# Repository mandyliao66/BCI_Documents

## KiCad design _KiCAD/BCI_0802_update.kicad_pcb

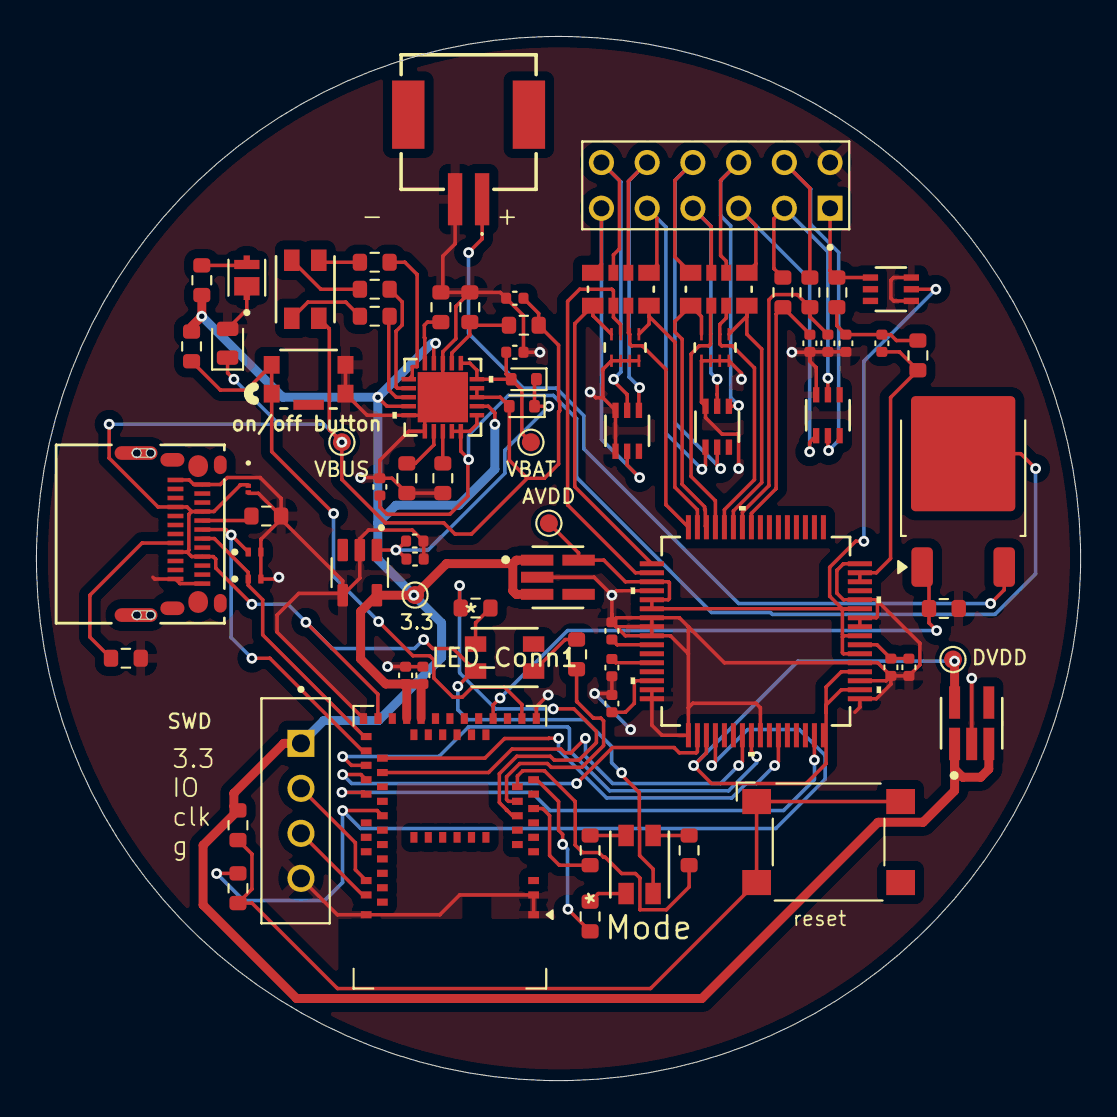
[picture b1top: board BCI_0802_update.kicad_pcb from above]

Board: 2 copper layers, 58.0 x 58.0 mm, 76 parts (0 on the bottom side), 72 nets.

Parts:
C1, C3, C7, C10, C12: 1uF; C_0402_1005Metric
C2, C4, C17: 10uF; C_0402_1005Metric
C5, C18, C19, C20: 1000pF; C_0402_1005Metric
C6: 0.1uF; C_0402_1005Metric
C11: 100uF; C_0402_1005Metric
C15, C16: 4.7uF; C_0402_1005Metric
C21, C24: CKCL44X7R1H102M085AA; CKCL44_TDK
CR1: ESD441DPLR; X2SON2_DPL_TEX
D1, D2: 1N4148WT; D_SOD-523
D3, D5: ESD321DPYR; TVS_ESD321DPYR
D4: MP-2016-1100-50-70; LED_MP-2016-1100-50-70
D6: BZM55Bxx; D_MicroMELF
J1: SM02B-ZESS-TB_LF__SN_; SM02BZESSTBLFSN
J2: 87227-6; TE_87227-6
J3: B4B-EH-A; JST_B4B-EH-A
LED_Conn1: CLV1A-FKB-CK1VW1DE1BB7C3C3; CLV1A-FKB-CK1VW1DE1BB7C3C3_CRE
LED_Op_Mode1: CLV1A-FKB-CK1VW1DE1BB7C3C3; CLV1A-FKB-CK1VW1DE1BB7C3C3_CRE
LED_chargingstate1: CLV1A-FKB-CK1VW1DE1BB7C3C3; CLV1A-FKB-CK1VW1DE1BB7C3C3_CRE
Q1: SUD08P06-155L; TO-252-2
R1, R4: 5.1k; R_0603_1608Metric
R2, R5, R8: 10k; R_0603_1608Metric
R3: 1M; R_0603_1608Metric
R6: 110k; R_0603_1608Metric
R7: 330k; R_0603_1608Metric
R9, R10, R11, R18, R19, R21, R23, R24: 470; R_0603_1608Metric
R12, R13, R14, R15, R16: 2.2k; R_0603_1608Metric
R17, R22: CAY16-2201F4LF; CAY16_BRN
R20, R25: 33; R_0603_1608Metric
R26: 4.7k; R_0603_1608Metric
S1: B3FS-4002P; SW_SPST_Omron_B3FS-100xP
SW1: KMR221GLFS; SW4_KMR221GLFS_CNK
TP1: VBUS; TestPoint_Pad_D1.0mm
TP2: VBAT; TestPoint_Pad_D1.0mm
TP3: 3.3; TestPoint_Pad_D1.0mm
TP4: AVDD; TestPoint_Pad_D1.0mm
TP5: DVDD; TestPoint_Pad_D1.0mm
U1: USB-C31-S-RA-CS2-SMT-BK-T/R; USB-C31-S-RA-CS2-SMT-BK-T&slash_R_ADM
U2: ADS1299-4PAG; PAG64_TEX
U3: TPS78233DDCT; SOT95P280X110-5N
U4: TPS7A2030PDBVR; DBV0005A-IPC_A
U5: TPS7A2018PDBVR; DBV0005A-IPC_A
U6: MCP73871-2AAI/ML; QFN20_4x4MC_MCH
U7, U8, U9, U11: TPD4E1B06DCKR; DCK6_TEX
U10: MDBT50Q-1MV2; Raytac_MDBT50Q

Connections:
/1N: J2.5, R22.1, U8.4 (IO3)
/1P: J2.11, R22.2, U9.1 (IO1)
/2N: J2.4, R17.3, U8.2 (IO2)
/2P: J2.10, R17.4, U8.5 (IO4)
/3.3V: C2.2, C3.2, J3.1, R2.2, R5.2, R26.2, TP3.1, U3.5 (OUT), U4.1 (IN), U4.3 (EN), U5.1 (IN), U5.3 (EN), U6.4 (PROG2), U6.9 (*TE), U6.17 (CE), U10.28 (VDD), U10.30 (VDDH)
/3N: J2.3, R17.1, U7.4 (IO3)
/3P: J2.9, R17.2, U8.1 (IO1)
/4N: J2.2, R15.2, U7.2 (IO2)
/4P: J2.8, R16.2, U7.5 (IO4)
/AVDD: TP4.1, U2.19 (AVDD), U2.21 (AVDD), U2.22 (AVDD), U2.54 (AVDD1), U2.56 (AVDD), U2.59 (AVDD), U4.5 (OUT), U11.2 (IO2)
/BAT+: J1.1, Q1.3 (S)
/BIAS: J2.1, R14.2, U11.4 (IO3)
/BIAS_DRV: C5.1, C20.2, R3.1, R14.1
/Button_on: R5.1, SW1.1, SW1.2, U10.16 (P0.27)
/CS: U2.39 (*CS), U10.38 (P0.16)
/DNEG: D5.1, U1.A7 (DN1), U10.34 (D-)
/DPOS: D3.1, U1.A6 (DP1), U10.35 (D+)
/DRDY: U2.47 (*DRDY), U10.41 (P0.17)
/DVDD: TP5.1, U2.35 (*PWDN), U2.48 (DVDD), U2.50 (DVDD), U2.52 (CLKSEL), U5.5 (OUT)
/IN1N: C24.5, R22.8, U2.15 (IN1N)
/IN1P: C24.6, R22.7, U2.16 (IN1P)
/IN2N: C21.7, R17.6, U2.13 (IN2N)
/IN2P: C21.8, R17.5, U2.14 (IN2P)
/IN3N: C21.5, R17.8, U2.11 (IN3N)
/IN3P: C21.6, R17.7, U2.12 (IN3P)
/IN4N: C19.2, R15.1, U2.9 (IN4N)
/IN4P: C18.2, R16.1, U2.10 (IN4P)
/MISO: U2.43 (DOUT), U10.36 (P0.14)
/MOSI: U2.34 (DIN), U10.39 (P0.15)
/RESET: R25.1, U2.36 (*RESET), U10.43 (P0.21)
/SCLK: U2.40 (SCLK), U10.37 (P0.13)
/SRB1: J2.6, R22.4, U9.5 (IO4)
/SRB2: J2.12, R22.3, U9.2 (IO2)
/SWDCLK: J3.3, U10.53 (SWDCLK)
/SWDIO: J3.2, U10.51 (SWDIO)
/VBAT: C16.2, Q1.2 (D), U6.14 (VBAT), U6.15 (VBAT), U6.16 (VBAT_SENSE)
/VBAT_OUT: C15.2, D1.2 (A), TP2.1, U6.1 (OUT), U6.20 (OUT)
/VBUS: C17.2, CR1.1 (I/O), D2.2 (A), D6.1 (K), LED_Conn1.2, LED_Op_Mode1.2, LED_chargingstate1.2, R7.2, TP1.1, U1.A4 (VBUS), U1.A9 (VBUS), U1.B4 (VBUS), U1.B9 (VBUS), U6.18 (IN), U6.19 (IN), U10.32 (VBUS)
/_SRB1: C24.8, R22.5, U2.17 (SRB1)
/_SRB2: C24.7, R22.6, U2.18 (SRB2)
GNDA: C1.2, C2.1, C3.1, C4.1, C6.2, C7.2, C10.2, C11.2, C12.2, C15.1, C16.1, C17.1, C18.1, C19.1, C20.1, C21.1, C21.2, C21.3, C21.4, C24.1, C24.2, C24.3, C24.4, CR1.2 (GND), D3.2, D4.C, D5.2, D6.2 (A), J1.2, J3.4, R1.1, R4.2, R6.2, R8.2, R12.1, R13.1, R20.2, SW1.3, SW1.4, U1.A1 (GND), U1.A12 (GND), U1.B1 (GND), U1.B12 (GND), U2.20 (AVSS), U2.23 (AVSS), U2.24 (VREFP), U2.25 (VREFN), U2.31 (RESV1), U2.32 (AVSS), U2.33 (DGND), U2.41 (DAISY_IN), U2.49 (DGND), U2.51 (DGND), U2.53 (AVSS1), U2.57 (AVSS), U2.58 (AVSS), U2.60 (BIASREF), U2.64 (RESERVED), U3.2 (GND__1), U3.4 (GND), U4.2 (GND), U5.2 (GND), U6.3 (SEL), U6.10 (VSS), U6.11 (VSS), U6.21 (EP), U7.3 (GND), U8.3 (GND), U9.3 (GND), U9.4 (IO3), U10.1 (GND), U10.2 (GND), U10.15 (GND), U10.33 (GND), U10.55 (GND), U11.1 (IO1), U11.3 (GND)
unnamed: C1.1, C4.2, D1.1 (K), D2.1 (K), U3.1 (IN)
unnamed: D4.A, R2.1
unnamed: LED_Conn1.1, R19.2
unnamed: LED_Conn1.3, R18.2
unnamed: LED_Op_Mode1.1, R24.2
unnamed: LED_Op_Mode1.3, R21.2
unnamed: LED_Op_Mode1.4, R23.2
unnamed: LED_chargingstate1.1, R11.2
unnamed: LED_chargingstate1.3, R9.2
unnamed: LED_chargingstate1.4, R10.2
unnamed: Q1.1 (G), R20.1, U10.18 (P0.01)
unnamed: R25.2, R26.1, S1.1, S1.2
unnamed: R1.2, U1.A5 (CC1)
unnamed: R4.1, U1.B5 (CC2)
unnamed: C5.2, R3.2, U2.62 (BIASINV), U2.63 (BIASOUT)
unnamed: C11.1, U2.28 (VCAP1)
unnamed: C12.1, U2.30 (VCAP2)
unnamed: C6.1, C7.1, U2.55 (VCAP3)
unnamed: C10.1, U2.26 (VCAP4)
unnamed: R9.1, U6.6 (*PG)
unnamed: R12.2, U6.13 (PROG1)
unnamed: R13.2, U6.12 (PROG3)
unnamed: R11.1, U6.8 (STAT1/*LBO)
unnamed: R10.1, U6.7 (STAT2)
unnamed: R8.1, U6.5 (THERM)
unnamed: R6.1, R7.1, U6.2 (VPCC)
unnamed: R18.1, U10.11 (P0.02)
unnamed: R19.1, U10.9 (P0.03)
unnamed: R21.1, U10.13 (P0.28)
unnamed: R23.1, U10.10 (P0.29)
unnamed: R24.1, U10.14 (P0.30)

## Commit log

2025-08-02 Rename Screenshot 2025-08-02 at 9.13.21 PM.png to 3D_PCB_Front
2025-08-02 Rename Screenshot 2025-08-02 at 9.14.00 PM.png to 3D_PCB_Back.png
2025-08-02 Rename 3D_PCB_Front to 3D_PCB_Front.png
